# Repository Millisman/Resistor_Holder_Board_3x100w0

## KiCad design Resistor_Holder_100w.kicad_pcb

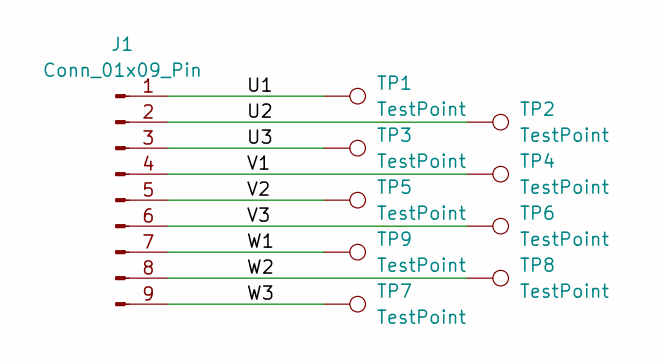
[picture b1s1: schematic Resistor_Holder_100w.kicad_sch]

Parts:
J1: Conn_01x09_Pin; PhoenixContact_MC_1,5_9-G-5.08_1x09_P5.08mm_Horizontal
TP1, TP2, TP3, TP4, TP5, TP6, TP7, TP8, TP9: TestPoint; TestPoint_Loop_D1.80mm_Drill1.0mm_Beaded

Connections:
/U1: J1.1, TP1.1
/U2: J1.2, TP2.1
/U3: J1.3, TP3.1
/V1: J1.4, TP4.1
/V2: J1.5, TP5.1
/V3: J1.6, TP6.1
/W1: J1.7, TP9.1
/W2: J1.8, TP8.1
/W3: J1.9, TP7.1

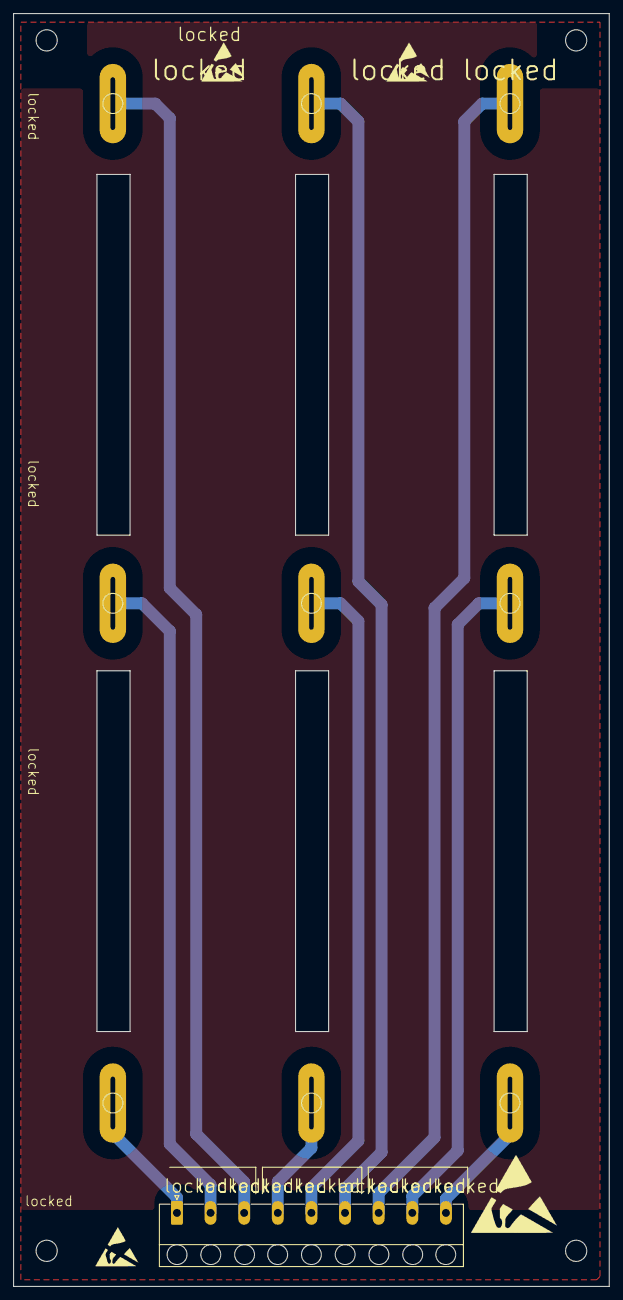
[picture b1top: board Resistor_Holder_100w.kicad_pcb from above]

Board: 2 copper layers, 90.0 x 192.3 mm, 10 parts (0 on the bottom side), 9 nets.

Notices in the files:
Resistor_Holder_100w.kicad_pcb:
Designed by Sergey Kostanoy (c) 2023 in USA
